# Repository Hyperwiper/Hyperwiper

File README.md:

# hyperwiper
Basic idea is that most normal songs have a consistent (or at least slowly changing) rhythm that can be used as a “click track” for dancers, including robotic windshield wipers. By hiding the sound of wipers in the rhythm (a kind of masking), cabin signal-noise ratio can be enhanced. Many car drivers and  riders enjoy listening to music while driving, and support of cross-modal, synaesthetic stimulus can enhance that experience, a kind of visual music.

Data flow: audio source such as music player or smartphone connected to beat detector as embedded

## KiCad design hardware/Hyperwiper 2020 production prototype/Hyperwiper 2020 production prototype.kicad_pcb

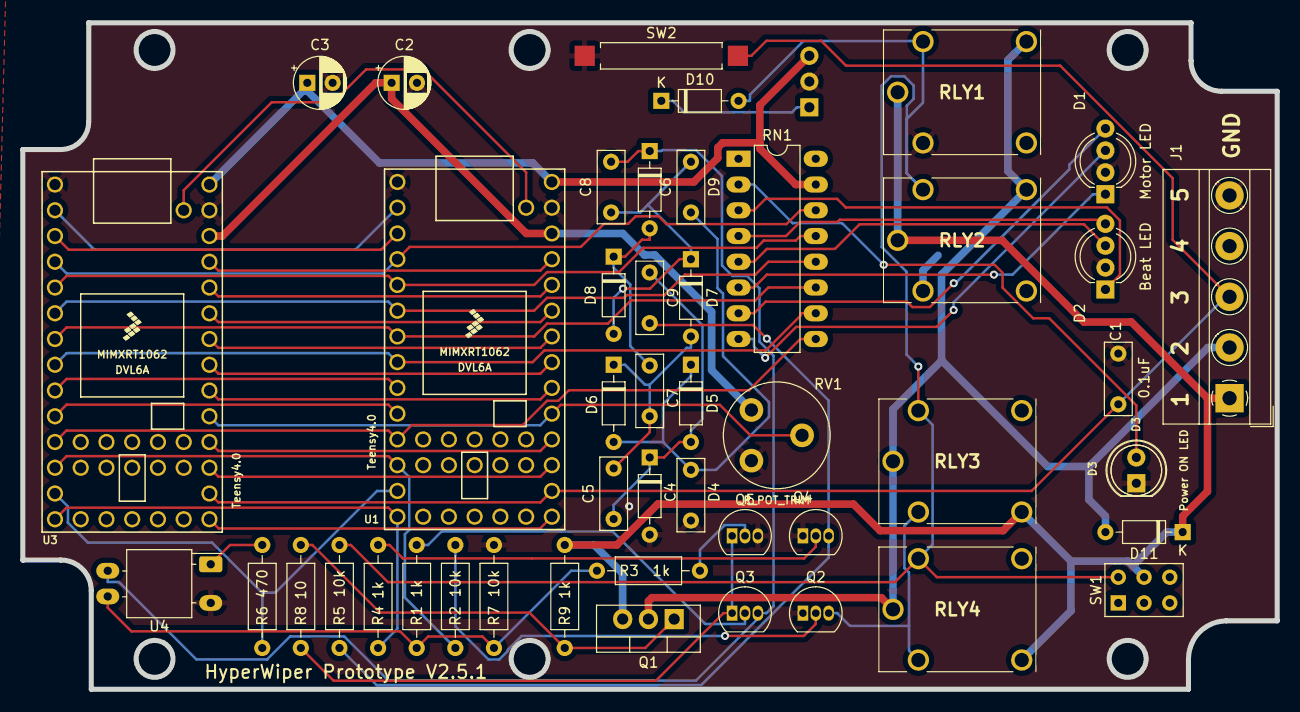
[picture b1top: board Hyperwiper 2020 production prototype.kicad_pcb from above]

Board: 2 copper layers, 123.8 x 65.8 mm, 47 parts (1 on the bottom side), 55 nets.

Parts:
C1, C4, C5, C6, C7, C8, C9: 0.1uF; C_Rect_L7.0mm_W2.5mm_P5.00mm
C2, C3: 100uF; CP_Radial_D5.0mm_P2.50mm
D1: Motor LED; LED_D5.0mm-4_RGB_Wide_Pins
D2: Beat LED; LED_D5.0mm-4_RGB_Wide_Pins
D3: Power ON LED; LED_D5.0mm_Clear
D4, D5, D6, D7, D8, D9, D10, D11: D; D_DO-35_SOD27_P7.62mm_Horizontal
J1: Conn_01x05; TerminalBlock_MetzConnect_Type011_RT05505HBWC_1x05_P5.00mm_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
Q1: IRF3205; TO-220-3_Vertical
Q2, Q3, Q4: 2N2222; TO-92_Inline
Q5: 2N3906; TO-92_Inline
R1, R3, R4, R9: 1k; R_Axial_DIN0207_L6.3mm_D2.5mm_P10.16mm_Horizontal
R2, R5, R7: 10k; R_Axial_DIN0207_L6.3mm_D2.5mm_P10.16mm_Horizontal
R6: 470; R_Axial_DIN0207_L6.3mm_D2.5mm_P10.16mm_Horizontal
R8: 10; R_Axial_DIN0207_L6.3mm_D2.5mm_P10.16mm_Horizontal
RLY1, RLY2, RLY3, RLY4: JSM1-12V-5; SRA12VDCCL
RN1: R_Pack08; DIP-16_W7.62mm_LongPads
RV1: R_POT_TRIM; Potentiometer_Piher_PT-10-V05_Vertical
SW1: SW_DPDT_x2; SW_NKK_G1xJP
SW2: SW_Reed; SW_SPST_REED_CT10-XXXX-G1
U1, U3: Teensy4.0; Teensy40
U2: OKI-78SR-5; Converter_DCDC_muRata_OKI-78SR_Horizontal
U4: NSL-32; Luna_NSL-32

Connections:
+3V3: C2.1, RV1.3, U1.31 (3V3), U3.31 (3V3)
/5V: C3.1, RN1.15 (R2.2), U1.33 (VIN), U2.3 (OUT), U3.33 (VIN)
/12V: D10.2 (A), R5.2, RLY1.5, RLY2.5, RLY3.5, RLY4.5, SW1.6 (C)
/A2: U1.2 (0_RX1_CRX2_CS1), U3.2 (0_RX1_CRX2_CS1)
/A3: U1.3 (1_TX1_CTX2_MISO1), U3.3 (1_TX1_CTX2_MISO1)
/A4: RN1.14 (R3.2), U1.4 (2_OUT2), U3.4 (2_OUT2)
/A5: RN1.13 (R4.2), U1.5 (3_LRCLK2), U3.5 (3_LRCLK2)
/A6: RN1.12 (R5.2), U1.6 (4_BCLK2), U3.6 (4_BCLK2)
/A7: RN1.11 (R6.2), U1.7 (5_IN2), U3.7 (5_IN2)
/A8: RN1.10 (R7.2), U1.8 (6_OUT1D), U3.8 (6_OUT1D)
/A9: U1.9 (7_RX2_OUT1A), U3.9 (7_RX2_OUT1A)
/A10: U1.10 (8_TX2_IN1), U3.10 (8_TX2_IN1)
/A11: RN1.9 (R8.2), U1.11 (9_OUT1C), U3.11 (9_OUT1C)
/A12: R2.1, U1.12 (10_CS_MQSR), U3.12 (10_CS_MQSR)
/A13: R6.1, U1.13 (11_MOSI_CTX1), U3.13 (11_MOSI_CTX1)
/A14: R4.1, U1.14 (12_MISO_MQSL), U3.14 (12_MISO_MQSL)
/A20: U1.20 (13_SCK_CRX1_LED), U3.20 (13_SCK_CRX1_LED)
/A21: C1.1, J1.3, SW2.1, U1.21 (14_A0_TX3_SPDIF_OUT), U3.21 (14_A0_TX3_SPDIF_OUT)
/A22: U1.22 (15_A1_RX3_SPDIF_IN), U3.22 (15_A1_RX3_SPDIF_IN)
/A23: U1.23 (16_A2_RX4_SCL1), U3.23 (16_A2_RX4_SCL1)
/A24: RV1.2, U1.24 (17_A3_TX4_SDA1), U3.24 (17_A3_TX4_SDA1)
/A25: U1.25 (18_A4_SDA0), U3.25 (18_A4_SDA0)
/A26: U1.26 (19_A5_SCL0), U3.26 (19_A5_SCL0)
/A27: U1.27 (20_A6_TX5_LRCLK1), U3.27 (20_A6_TX5_LRCLK1)
/A28: U1.28 (21_A7_RX5_BCLK1), U3.28 (21_A7_RX5_BCLK1)
/B21: U1.34 (VUSB), U3.34 (VUSB)
/B25: U1.30 (23_A9_CRX1_MCLK1), U3.30 (23_A9_CRX1_MCLK1)
/B26: U1.29 (22_A8_CTX1), U3.29 (22_A8_CTX1)
GND: C1.2, C2.2, C3.2, C4.1, D1.2 (K), D2.2 (K), D3.1 (K), D4.2 (A), J1.5, Q2.1 (E), Q4.1 (E), Q5.3 (C), R7.2, RLY1.2, RLY2.2, RV1.1, SW2.2, U1.1 (GND), U1.32 (GND), U2.2 (GND), U3.1 (GND), U3.32 (GND), U4.2 (K)
unnamed: D1.3 (BA), RN1.8 (R8.1)
unnamed: D1.4 (GA), RN1.7 (R7.1)
unnamed: D1.1 (RA), RN1.6 (R6.1)
unnamed: D2.3 (BA), RN1.5 (R5.1)
unnamed: D2.4 (GA), RN1.4 (R4.1)
unnamed: D2.1 (RA), RN1.3 (R3.1)
unnamed: D3.2 (A), RN1.2 (R2.1)
unnamed: C5.1, C9.2, D4.1 (K), D5.2 (A)
unnamed: C4.2, C6.1, D5.1 (K), D6.2 (A)
unnamed: C5.2, C7.1, D6.1 (K), D7.2 (A)
unnamed: C6.2, C8.1, D7.1 (K), D8.2 (A)
unnamed: C7.2, D8.1 (K), D9.2 (A)
unnamed: C8.2, D9.1 (K), Q3.3 (C), U4.4 (R)
unnamed: D10.1 (K), U2.1 (IN)
unnamed: D11.2 (A), J1.2, Q1.2 (D), RLY1.4, RLY2.4, RLY3.1, RLY4.1
unnamed: D11.1 (K), J1.1, Q1.3 (S), R9.2, RLY1.1, RLY2.1, RLY3.3, RLY4.3, SW1.5 (B)
unnamed: Q1.1 (G), R8.2, R9.1
unnamed: Q2.2 (B), R2.2
unnamed: Q2.3 (C), RLY3.2, RLY4.2
unnamed: Q3.2 (B), R1.2
unnamed: Q3.1 (E), Q5.1 (E), R8.1
unnamed: Q4.2 (B), R4.2
unnamed: C9.1, Q4.3 (C), R5.1
unnamed: Q5.2 (B), R3.2
unnamed: R6.2, U4.1 (A)
unnamed: R1.1, R3.1, R7.1, U4.3 (R)

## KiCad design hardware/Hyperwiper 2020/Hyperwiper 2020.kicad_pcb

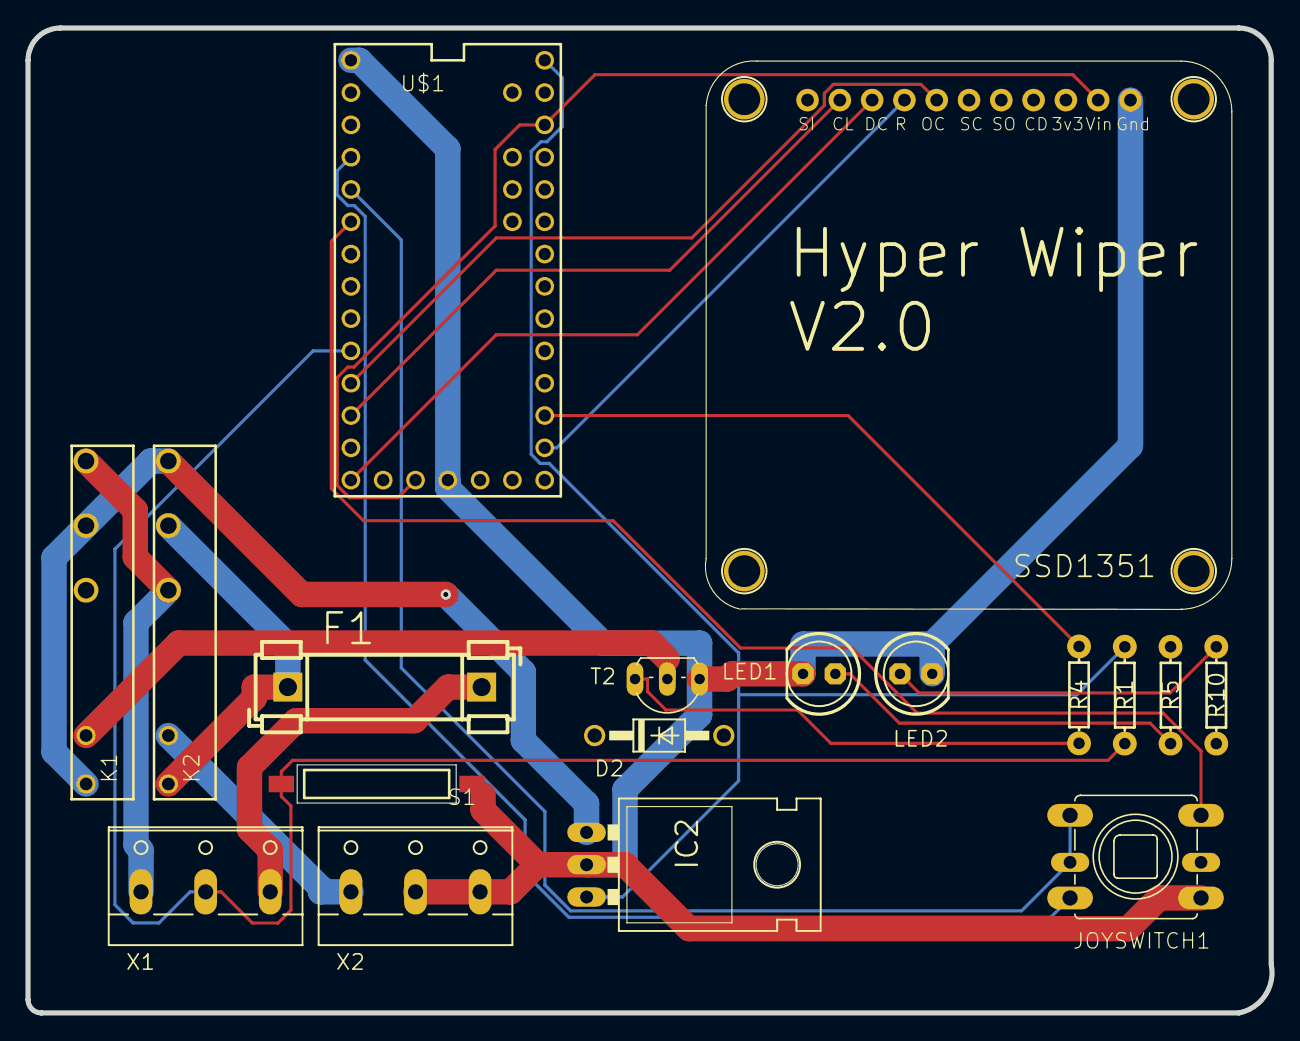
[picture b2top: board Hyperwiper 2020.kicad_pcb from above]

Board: 2 copper layers, 97.8 x 77.5 mm, 18 parts (0 on the bottom side), 21 nets.

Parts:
D2: 1N4004; DO41-10
F1: FUSE; FUSE_HOLDER_5X20MM
IC2: V_REG_78XX-TO-220; TO-220-ALT
JOYSWITCH1: JoySwitch; SKQU
K1, K2: SNR?0-bGeigieNanoKit_V1.1r5a-eagle-import; SNR-V
LED1, LED2: LED5MM
R1, R4: 10k; AXIAL-0.3EZ
R5: 470; AXIAL-0.3EZ
R10: 1k; AXIAL-0.3EZ
S1: REED-Switch; CT10-A2
SSD1351: SSD1351_128X128_LCD
T2: 2SC1815; TO92-ECB
U$1: TEENSY 4; TEENSY_3.0+4
X1, X2: W237-3E

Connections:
/D2: JOYSWITCH1.DOWN, U$1.2
/D3: JOYSWITCH1.LEFT, JOYSWITCH1.UP, U$1.3
/D4: JOYSWITCH1.CENTER, U$1.4
/D8: R1.P$1 (1), S1.2, U$1.8, X1.2 (KL)
/D10: SSD1351.JP1$10 (CL), U$1.10
/VCC: SSD1351.JP1$7 (VDD), U$1.3.3V, U$1.3.3V1 (3.3V)
/VDD: IC2.OUT, R1.P$2 (2), U$1.VIN
GND: IC2.GND, JOYSWITCH1.COMMON, LED1.K (C), LED2.K (C), S1.1, SSD1351.JP1$8 (GND), T2.E, U$1.GND, U$1.GND1 (GND), X2.2 (KL), X2.3 (KL)
unnamed: IC2.IN, K1.11, K1.A1 (1), K2.14 (S)
unnamed: K1.A2 (2), T2.C
unnamed: F1.1, K2.11, K2.A1 (1)
unnamed: F1.2, X1.3 (KL)
unnamed: K1.14 (S), K2.12 (O), X1.1 (KL)
unnamed: K2.A2 (2), X2.1 (KL)
unnamed: LED1.A, R5.P$1 (1)
unnamed: LED2.A, R10.P$2 (2)
unnamed: R4.P$1 (1), U$1.15/A1
unnamed: R4.P$2 (2), T2.B
unnamed: SSD1351.JP1$1 (RST), U$1.14/A0
unnamed: SSD1351.JP1$2 (OC), U$1.9
unnamed: SSD1351.JP1$11 (DC), U$1.12

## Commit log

2020-06-05 Teensy4 setup for VSCodium
2020-06-05 Updated version error.
2020-06-07 Added Kicad files
2020-06-08 Upated version to V2.0.0
2020-06-08 Updated Kicad schematic
2020-06-16 Updated Kcad files
2020-06-17 New Prototype board for software
2020-06-19 fix some typoos
2020-06-20 Test for Teensy 4 pins and SSD1351
2020-06-20 Updated ProtoType drawings
2020-06-21 Updated schemtics and board
2020-06-22 Rotate the screen 180 degree.
2020-06-22 Renamed DWP to HyperWiper
2020-06-24 Set theme jekyll-theme-minimal
2020-06-24 Create LICENSE
2020-06-24 Update issue templates
2020-06-24 U@dated date on prototype board
2020-06-24 test for updates
2020-06-28 Added notes
2020-07-20 Updated schematic/pcb
2020-07-22 Updated boards and libraries fro Kicad
2020-07-22 Updated PCB
2020-07-28 Prototype production draft board.
2020-07-28 Updates schematic and PCB boards
2020-07-29 Update Schematics and PCB
2020-07-30 Updated darft schemetics and board.
2020-07-30 Took out the joystick and display funtions.
2020-07-30 Updated Schematic and board.
2020-07-30 ticks generator V0.3
2020-07-31 Update Schematic and boards
2020-08-04 Updated boards.
2020-08-04 Added some mod to the 3 D audio board
2020-08-09 updated kicad files with new traced board
2020-08-13 Updated boards
2020-08-15 Updated board
2020-08-19 Updated schematic
2020-09-06 Changes schemtic. Mistake in wireing
2020-09-10 Adde routing for the RGB leds
2020-09-10 Updated pin numbers
2020-09-11 Updated schematics
2020-09-12 added tests for LEDS and updated the schematics
2020-09-12 Added flowchart drafts and modified pin number after finding conflics with the audio board I2C bus
2020-09-13 Assined pins and updated firmware
2020-09-16 Test for magnet arrving and leaving logic
2020-09-17 Added bounch for magnet sensor tests.
2020-09-18 Update schematics and started timing diagram.
2020-09-20 Changed motorLED LED magnet arriving and leaving
2020-09-21 Adde audio timing flow chart
2020-09-23 Updated timingplot and changed RBG LED programming
2020-09-23 Updated diagrams
2020-09-28 Updated plots graph and DWP ino updated
2020-10-01 adding basic bpm detector
2020-10-01 added infro for Takachi case modification.
2020-10-02 added doxygen generated html file for analyzing
2020-10-02 updated doxygen files
2020-10-04 Updated timing plot
2020-10-08 added new timing plot
2020-10-08 Added storage setup for Teensy 4 in EEPROMex.h
2020-10-15 Upadted PlatformIO for Beat=Detection_2020 file
2020-10-15 Updated delay function
2020-10-15 Updated deley function fix code
2020-10-17 updated DWP.ino with code from Julian and Camlio
2020-10-17 Updated version number in serial output on startup
2020-10-18 updated code for test runs
2020-10-18 calculate start motor to reach reedswitch time
2020-10-21 Updated code for test reruen wiper
2020-10-21 Updated version information.
2020-10-21 Updated test minloop (6 seconds) run.
2020-10-21 Updated serial plotting.
2020-10-22 Cleanup code
2020-10-24 Motor running from the beat beat code.
2020-10-26 Changed monitor speed back to 9600.
2020-10-31 Started code for missing beat detection
2020-11-01 Setuo potmeter reading and pot meter timing
2020-11-07 updated board and code
2020-11-09 Added diode for protection wireing of power.
2020-11-09 Update code for disbale beat detection by rob
2020-11-13 Updated files
2020-11-15 Updated board information
2020-11-15 Updated timeing graph
2020-11-15 Updated chart timing plots
2020-11-18 Updated board for using 2x Xbee RX/TX for furure.
2020-11-22 Added article Figures
2020-11-29 updated test for checking logic
2020-11-29 Updated schematic
2020-11-30 Updated graphs
2020-11-30 updated code for improved logic for beatLED
2020-12-03 Updated code for potmeter reading
2020-12-03 Update delay for next beat calculated 1wipe+ pot
2020-12-05 Updated board with Xbee's
2020-12-06 Update code for one test wipe at startup.
2020-12-07 Updated graphics for manuscript
2020-12-07 Updated with startup bug fix
2020-12-07 Code cleanup and fixes for the stop time.
2020-12-07 Added extra infor for serial port trouble shooting
2020-12-07 Added orange beat LED for visual beat detection
2020-12-07 Updated version info
2020-12-10 Updated for beat array construction.
2020-12-11 Updated board for Xbee BLE
2020-12-11 Updated flow chart and manuscript added
2020-12-12 Update code for beat LED display to show beats.
2020-12-12 Added 30BPM test track
2020-12-12 V2.1.8 added LED display beats
2020-12-14 Updated board with Xbee BLE setup
2020-12-31 Update board with caps, code: delay return wiper
2020-12-31 Update code for adjusting wiper retrun position
2021-01-04 V2.2.2 uncommented code for wipe test and delays.
2021-01-04 Upadted version info
2021-01-04 Fix for reading potmeter in percentages.
2021-01-07 Added svg file for lasercutting the wuperlift mod
2021-01-07 mapped timing pot to 60/130BPM
2021-01-07 Updated the version
2021-01-21 V2.2.4
2021-01-22 Updated text on board
2021-01-29 Update files
2021-01-29 Updated board with MOSFET IRF540N
2021-01-31 Updated board for MosFet
2021-02-05 Updated schematic for MOSFET
2021-02-08 Updated board for level chnages MOSFET.
2021-02-13 Updated schematic to V2.1.6 (MOSFETS)
2021-02-13 Updated board for new layout
2021-02-15 fixed schematic text
2021-02-15 added libraries for PWM control
2021-02-15 Removed serial read of sensor in PWM. Not in use.
2021-02-15 Added display messages serial port
2021-02-17 Fixed boot code
2021-03-01 Test
2021-03-02 kicad test
2021-03-07 Modofication for board 2.2.7
2021-03-14 test for restore
2021-03-14 More cleanup code
2021-03-14 Cleaned up more
2021-03-16 Update pot read variable
2021-03-18 Test for leaving wiper and double detect magnet.
2021-03-18 code fixes for start/stop/start bug . not fixed
2021-03-19 pot delay between the beat detect and run motor
2021-03-19 Updated description in header and version up
2021-03-20 added notes for start motor potmeter delay
2021-03-21 added delay_run_motor code
2021-03-22 Better delay pot run setup.
2021-03-24 Fixed some text
2021-03-24 Update schematic for MOSFETS
2021-03-24 Changed for V2.3.0
2021-03-25 Tested PWM 100%
2021-03-27 Updated for MOSFET hookup mistake
2021-03-28 Fixed issue with MosFet
2021-03-28 Setup for tesing MOSFET code
2021-03-29 Code for running MOSFET
2021-03-29 Updated versioning comment
2021-04-12 Updated boards with resistor block and moved parts
2021-04-14 tested for new hardware V2.3.0
2021-04-14 reverced the magnet logic
2021-04-15 Updated board to V2.4.0 with relay and usb out
2021-04-19 reset routing
2021-05-04 updated version
2021-05-05 updated code for mosfet
2021-05-05 Revert "V2.2.4"
    This reverts commit 82353572d8a5ac2a54fb88cb5b01a567b2c9fa1c.
2021-05-05 test for troubleshooting
2021-05-05 Modified V2.3.0 good working
2021-05-05 Updated version number
2021-05-05 V2.3.2 beat detection and controle working
2021-05-06 restore backup issue solved
2021-05-06 fixed schematic
2021-05-13 Version update
2021-05-18 Updated code for better delay timing pot meter
2021-05-19 Test for N-ch MOSFET 100A high end
2021-05-20 Updated schematic for N-CH MOSFET switching
2021-05-27 Updates board
2021-05-27 Updated board V2.4.1
2021-05-31 Updated board with protection diode and fixed some routing issues.
2021-06-03 V2.4.2 Updated for N-Channel MOSFET controle
2021-06-05 V 2.4.3 fixed interbeat setup
2021-06-10 Changed LM7805 to OKI-78SR
2021-06-13 Updated for Hyperwiper unit that had issues with pin 17 not reading data into the Teensy
2021-06-13 V2.4.4
2021-06-14 Cleaned up code
2021-06-17 Test for better timing of beats with serial plotter.
2021-06-17 V2.5.4 reset minloop time after motor is stopped.
2021-06-17 Reset minloop after baat detected. And fixed version number to V2.4.5
2021-06-17 Reversed minloop timing reset at beat
2021-06-18 Updated Schematic for V2.4.5 diodes drop.
2021-07-29 Updated for dual relays and no MOSFET
2021-08-12 Switched code for realy using
2021-08-12 Update header infor for relays.
2021-08-14 new idea for MOSfet use
2021-08-21 V2.51
2021-08-22 Updated board layout for use of MOSFET and relays. Setup for separate Teensy and Audio board (easy exchangable)
2021-08-24 Routed the new board
2021-08-25 Added extra transitor
2021-08-28 Init
2021-08-28 Added transsitor to 30V multiplier.
2021-08-29 added new Gerber files
2021-09-23 Updated board with fixed ground issue between the two transistors.
2021-09-26 Updated PWM2 code for generating 30V for N-Mosfet to be switched on/off
2021-09-27 Added text for new port for PWM1
2021-09-29 Updated board for footprint mistake relays.
2021-09-30 Added new schematic for proper MOSFET switching
2021-09-30 Disbaled MOSFET in code. And disabled 30V power.
2021-10-21 Tuning/debugging.
2021-10-21 V1.5.4 Updated for debugging
2021-10-23 V2.5.4 debugging
2021-10-24 V2.5.5 Test version
2021-10-26 Color RGB LEB test added.
2021-10-27 Test inbetween beats timeing.
2022-04-11 Update Doxygen
2022-04-19 Added Hall sensor
2022-05-27 Disabled delay and serial prints for faster beat detection
2022-05-27 Updated version numbering
2022-05-27 Disabled interbeats
2022-05-31 Setup test for interbeats
2022-07-04 Clean out some comments frist
2022-07-04 Suggested fix for bad delay function that wa s introduced for testing and implemented correctly
2022-07-05 Tested delay replacement funtions
2022-07-05 Tested old interbeat
2022-07-05 Confirmed hall mems sensor setup (for fufture use)
2022-07-09 V 2.6.0 optimized loop without delays.
2022-07-10 Minimized code
2022-07-10 Added data sheet for Hall sensor
2022-07-10 Small changes board
2022-07-12 Updated history
2022-07-13 120BPM test running track
2022-07-13 Rest time_pot after delay.
2022-07-13 disbaled serial prints
2022-07-16 Optimized code a bit more specially beatcounts
2022-07-19 Updated platformio.ini
2022-07-28 Chnaged code to output to headphones and line out L and R
2022-07-29 Change to master
2022-07-31 Changed audio output and checked new code
2022-07-31 Added counts to serial to be sure we have counts
2022-08-03 Updated board with Mens sensors for better magnet detetion
2022-08-03 Updated versions on schematic and board
2022-08-20 V2.6.6
2022-08-20 Update version
2022-08-20 Update version code
2022-08-20 Reset led
2022-08-20 Switch of Led after detection
